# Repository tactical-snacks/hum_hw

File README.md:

# hum

Hour Utilization Monitor: a coin-cell data logger that timestamps machine run time using an accelerometer and RTC.

## Hardware

| Function | Part |
|---|---|
| MCU | STM32U031K8U6 (Cortex-M0+, UFQFPN-32) |
| RTC clock | 32.768 kHz crystal, ABS07-120 |
| Accelerometer | LIS2DTW12 (I²C, INT1 → PA0, INT2 → PA2) |
| Storage | 24FC512, 64 KB I²C EEPROM |
| Power | CR2032 in Keystone 3034 holder |
| UI | Button (PA1), green LED (PA8) |
| Debug | SWD, ARM 10-pin header |
| Comms | UART, PA9 TX / PA10 RX |

## Operation

- MCU sleeps in Stop 2 with the RTC running.
- The accelerometer detects activity on its own and wakes the MCU.
- Run start/stop events are logged to EEPROM as epoch timestamps, in a wear-levelled ring buffer.
- Clock set and log download over UART.
- Target battery life: 5+ years.

## Jumpers

- **J4:** in series with the battery. Remove it to measure current.
- **J1:** 3.3 V bench input. **Open J4 first.** Never use 5 V.

## Tools

KiCad, STM32CubeMX / STM32CubeIDE.

See [power_budget.md](power_budget.md).

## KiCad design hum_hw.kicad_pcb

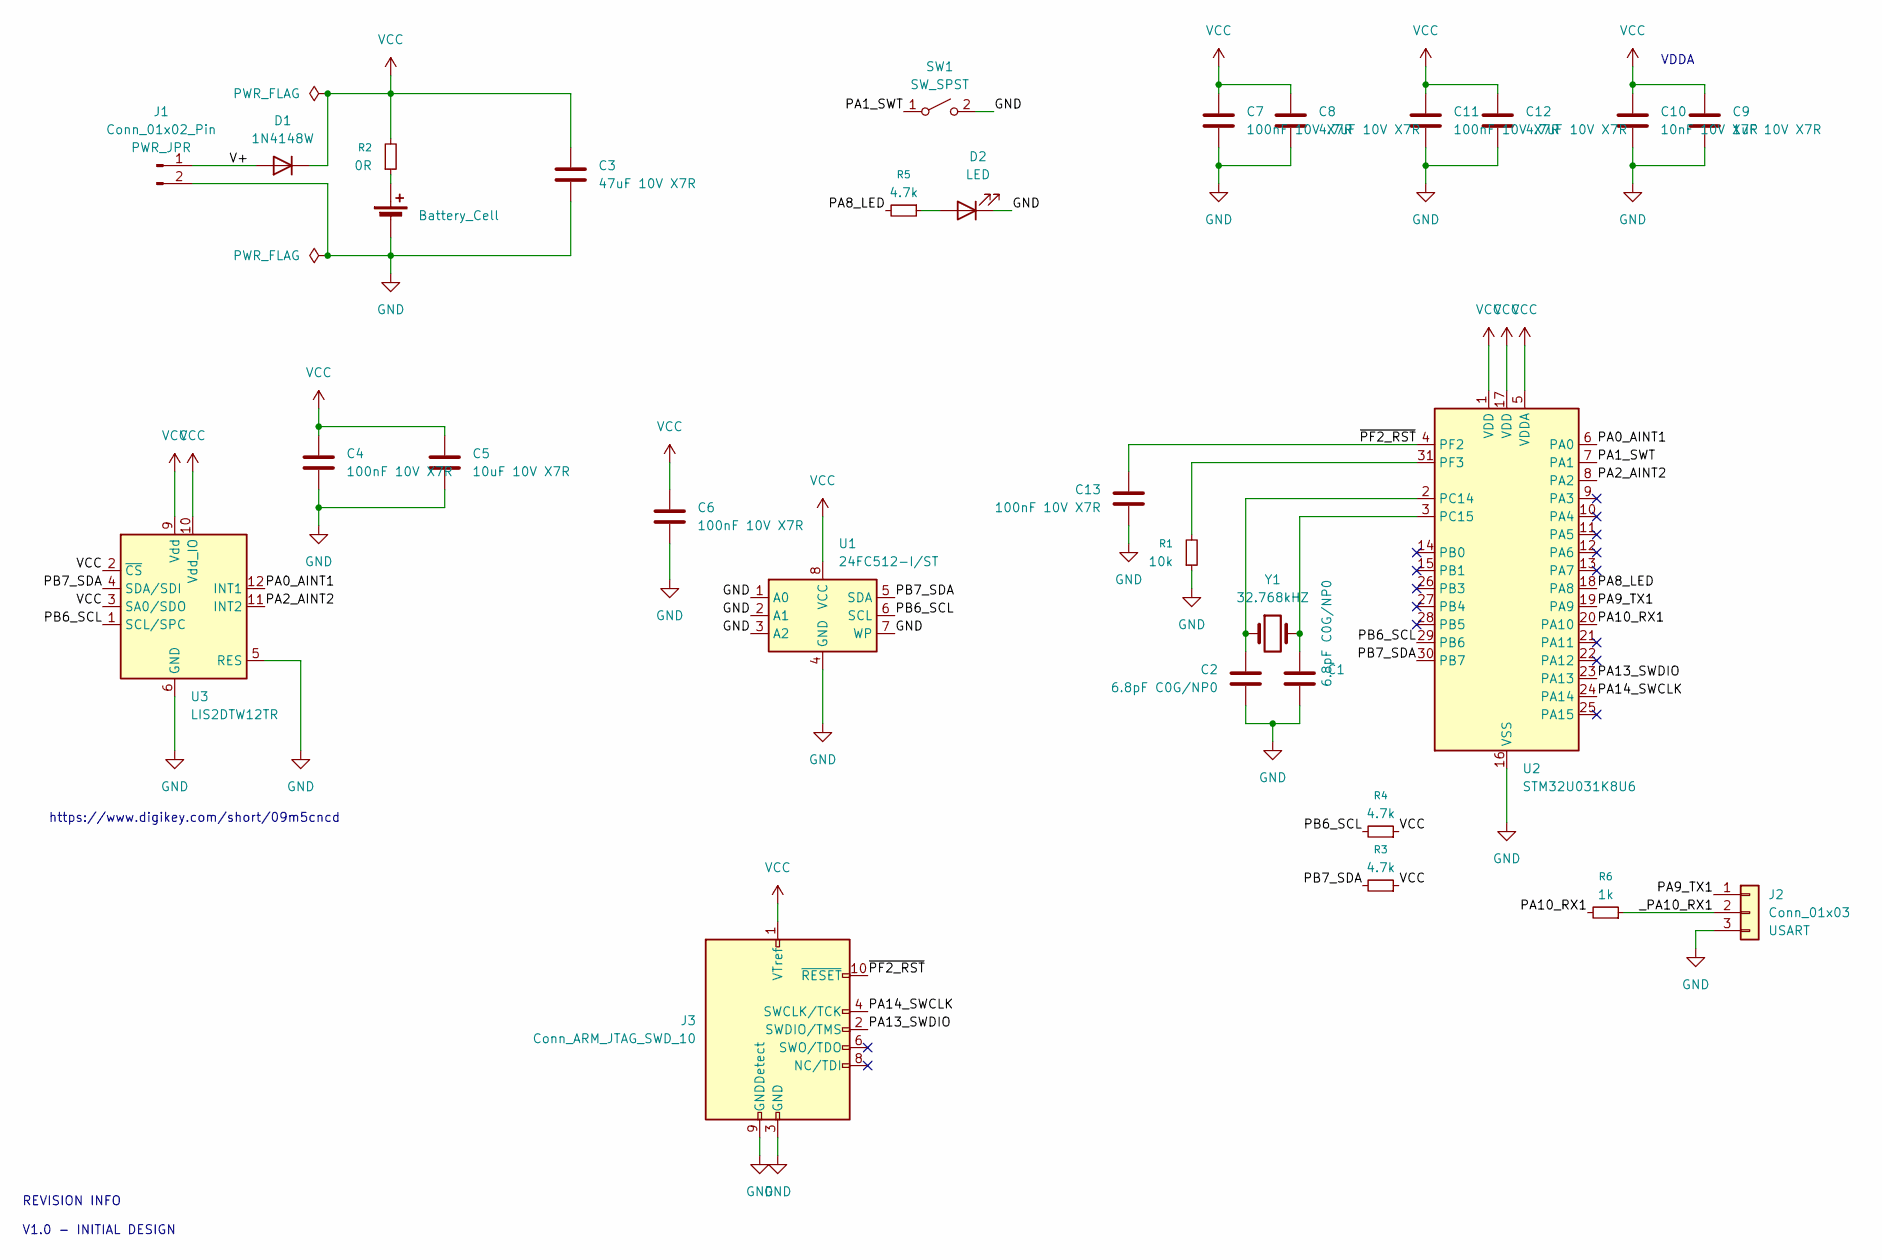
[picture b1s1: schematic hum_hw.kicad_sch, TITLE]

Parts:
BT1: Battery_Cell; BatteryHolder_Keystone_3034_1x20mm; MFR_PN 3034
C1, C2: 6.8pF C0G/NP0; C_0603_1608Metric
C3: 47uF 10V X7R; C_1210_3225Metric
C4, C6, C7, C11, C13: 100nF 10V X7R; C_0603_1608Metric
C5: 10uF 10V X7R; C_0805_2012Metric
C8: 4.7uF 10V X7R; C_0805_2012Metric
C9: 1uF 10V X7R; C_0603_1608Metric
C10: 10nF 10V X7R; C_0603_1608Metric
C12: 4.7uF 10V X7R; C_0603_1608Metric
D1: 1N4148W; D_SOD-123
D2: LED; LED_0805_2012Metric; MFR_PN LTST-C170TGKT
J1: Conn_01x02_Pin; PinHeader_1x02_P2.54mm_Vertical
J2: Conn_01x03; PinSocket_1x03_P2.54mm_Horizontal
J3: Conn_ARM_JTAG_SWD_10; PinHeader_2x05_P1.27mm_Vertical_SMD; MFR_PN BD125-10-A-0305-0580-L-B
R1: 10k; R_0805_2012Metric
R2: 0R; R_0805_2012Metric
R3, R4, R5: 4.7k; R_0805_2012Metric
R6: 1k; R_0805_2012Metric
SW1: SW_SPST; SW_SPST_PTS645Sx43SMTR92
U1: 24FC512-I/ST; TSSOP-8_4.4x3mm_P0.65mm; MFR_PN 24FC512-I/ST
U2: STM32U031K8U6; QFN-32-1EP_5x5mm_P0.5mm_EP3.45x3.45mm
U3: LIS2DTW12TR; LGA-12_2x2mm_P0.5mm; MFR_PN LIS2DTW12TR
Y1: 32.768kHZ; Crystal_SMD_3215-2Pin_3.2x1.5mm; MFR_PN ABS07-120-32.768KHZ-T

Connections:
/PA0_AINT1: U2.6 (PA0), U3.12 (INT1)
/PA1_SWT: SW1.1 (A), U2.7 (PA1)
/PA2_AINT2: U2.8 (PA2), U3.11 (INT2)
/PA8_LED: R5.2, U2.18 (PA8)
/PA9_TX1: J2.1, U2.19 (PA9)
/PA10_RX1: R6.2, U2.20 (PA10)
/PA13_SWDIO: J3.2 (SWDIO/TMS), U2.23 (PA13)
/PA14_SWCLK: J3.4 (SWCLK/TCK), U2.24 (PA14)
/PB6_SCL: R4.2, U1.6 (SCL), U2.29 (PB6), U3.1 (SCL/SPC)
/PB7_SDA: R3.2, U1.5 (SDA), U2.30 (PB7), U3.4 (SDA/SDI)
/V+: D1.2 (A), J1.1
/_PA10_RX1: J2.2, R6.1
/~PF2_RST: C13.1, J3.10 (~RESET), U2.4 (PF2)
GND: BT1.2 (-), C1.2, C2.2, C3.2, C4.2, C5.2, C6.2, C7.2, C8.2, C9.2, C10.2, C11.2, C12.2, C13.2, D2.1 (K), J1.2, J2.3, J3.3 (GND), J3.5 (GND), J3.9 (GNDDetect), R1.1, SW1.2 (B), U1.1 (A0), U1.2 (A1), U1.3 (A2), U1.4 (GND), U1.7 (WP), U2.16 (VSS), U2.32 (VSS), U2.33 (VSS), U3.5 (RES), U3.6 (GND), U3.7 (GND), U3.8 (GND)
unnamed: BT1.1 (+), R2.1
unnamed: D2.2 (A), R5.1
unnamed: C2.1, U2.2 (PC14), Y1.1
unnamed: C1.1, U2.3 (PC15), Y1.2
unnamed: R1.2, U2.31 (PF3)
VCC: C3.1, C4.1, C5.1, C6.1, C7.1, C8.1, C9.1, C10.1, C11.1, C12.1, D1.1 (K), J3.1 (VTref), R2.2, R3.1, R4.1, U1.8 (VCC), U2.1 (VDD), U2.5 (VDDA), U2.17 (VDD), U3.2 (~CS), U3.3 (SA0/SDO), U3.9 (Vdd), U3.10 (Vdd_IO)

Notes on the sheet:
VDDA
REVISION INFO V1.0 - INITIAL DESIGN
https://www.digikey.com/short/09m5cncd

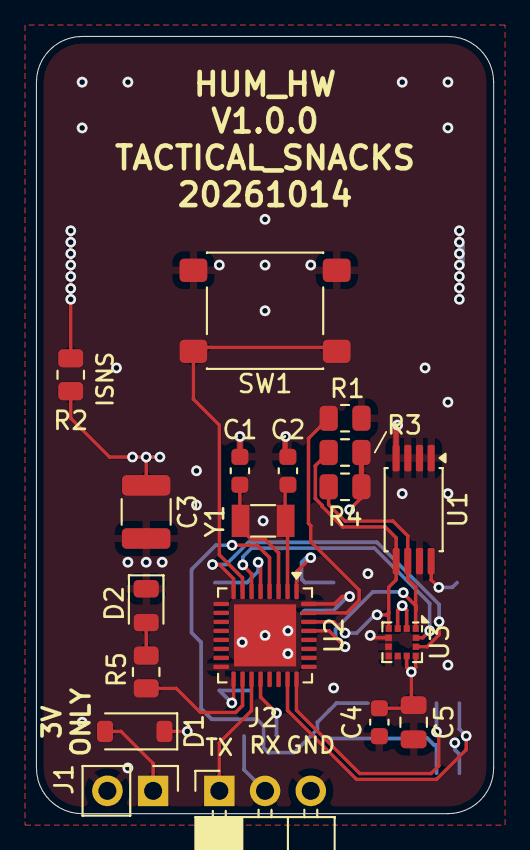
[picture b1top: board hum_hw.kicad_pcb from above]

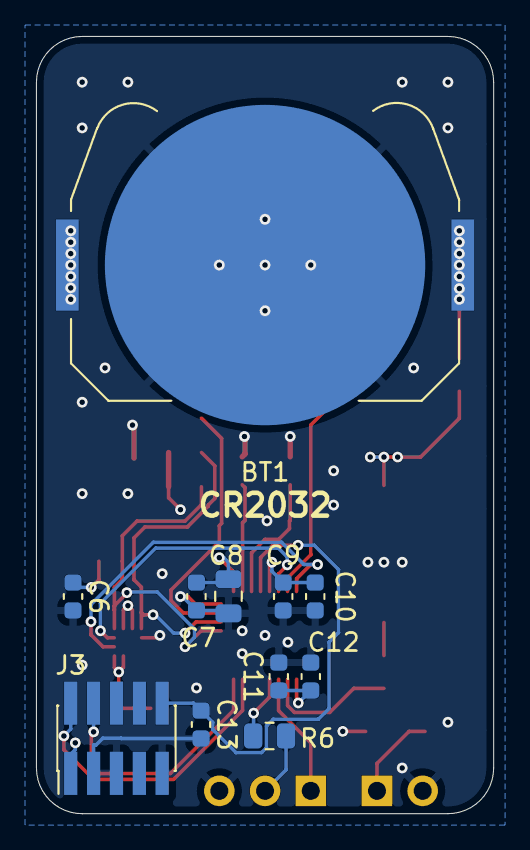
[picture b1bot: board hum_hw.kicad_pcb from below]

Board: 4 copper layers, 25.4 x 43.2 mm, 30 parts (11 on the bottom side), 20 nets.

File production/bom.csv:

Designator,Footprint,Quantity,Value,LCSC Part #
BT1,BatteryHolder_Keystone_3034_1x20mm,1,Battery_Cell,
"C1, C2",0603,2,6.8pF C0G/NP0,
C10,0603,1,10nF 10V X7R,
"C11, C13, C4, C6, C7",0603,5,100nF 10V X7R,
C12,0603,1,4.7uF 10V X7R,
C3,1210,1,47uF 10V X7R,
C5,0805,1,10uF 10V X7R,
C8,0805,1,4.7uF 10V X7R,
C9,0603,1,1uF 10V X7R,
D1,D_SOD-123,1,1N4148W,
D2,0805,1,LED,
J1,PinHeader_1x02_P2.54mm_Vertical,1,Conn_01x02_Pin,
J2,PinSocket_1x03_P2.54mm_Horizontal,1,Conn_01x03,
J3,PinHeader_2x05_P1.27mm_Vertical_SMD,1,Conn_ARM_JTAG_SWD_10,
R1,0805,1,10k,
R2,0805,1,0R,
"R3, R4, R5",0805,3,4.7k,
R6,0805,1,1k,
SW1,SW_SPST_PTS645Sx43SMTR92,1,SW_SPST,
U1,TSSOP-8_4.4x3mm_P0.65mm,1,24FC512-I/ST,
U2,QFN-32-1EP_5x5mm_P0.5mm_EP3.45x3.45mm,1,STM32U031K8U6,
U3,LGA-12_2x2mm_P0.5mm,1,LIS2DTW12TR,
Y1,Crystal_SMD_3215-2Pin_3.2x1.5mm,1,32.768kHZ,
